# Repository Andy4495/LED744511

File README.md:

# 74'4511 BCD to 7-Segment LED Library

This library for Arduino or Energia is designed to interface with the 74'4511 BCD to Seven Segment LED driver chip. The library also supports the use of an optional 74HC164 parallel out serial shift register to reduce output pin requirements.

The library supports either one or two 7-segment displays.

A reference design which can be used with the library is available in the [extras/hardware][1] folder.

## Supported Configurations

### Parallel-only Configuration

For a single digit, a minimum of 5 output pins are required:

+ BCD bit 3 (msb)
+ BCD bit 2
+ BCD bit 1
+ BCD bit 0 (lsb)
+ /LE (Latch Enable)
+ You can also optionally define the /LT and /BL signals

For two digit setups, a minimum of 6 output pins are required:

+ BCD bit 3 (msb)
+ BCD bit 2
+ BCD bit 1
+ BCD bit 0 (lsb)
+ /LE_1 (Latch Enable for most significant digit)
+ /LE_0 (Latch Enable for least significant digit)
+ You can also optionally define the /LT and /BL signals

### Serial Configuration with 74HC164

To reduce output pin usage with the 74HC164, the library assumes that the '164 pins are connected to the '4511 pins as follows:

```text
164    4511
---    ----
 QH ->  D0
 QG ->  D1
 QF ->  D2
 QE ->  D3
```

Output pins QA - QD are not used. A and B input pins should be tied together and are controlled by the "DATA_IN" pin.

For a single digit, a minimum of 3 output pins are required:

+ CLK
+ DATA_IN
+ /LE (Latch Enable)
+ You can also optionally define the /CLR ('164), /LT ('4511) and /BL ('4511) signals

For two digit setups, a minimum of 4 output pins are required:

+ CLK
+ DATA_IN
+ /LE_1 (Latch Enable for most significant digit)
+ /LE_0 (Latch Enable for least significant digit)
+ You can also optionally define the /CLR ('164), /LT ('4511) and /BL ('4511) signals

#### Decimal Points

In the serial configuration, it is possible to control the decimal points (8th segment) of the LED displays by using the unused output pins on the 74HC164 chip. Connect QD to the most significant decimal point driver signal and QC to the least significant decimal point driver signal. Note that both decimal point driver signals need current-limiting resistors, just like all the other LED segments controlled by the '4511 BCD chip.

To control the decimal points, first store the values with the `setDP(ms, ls)` method, and then call `writeBCD()` to send the values out the shift register and change the decimal point control lines.

## Usage

_See the sketches included in the `examples` folder._

First, include the library header file:

```cpp
#include "LED744511.h"
```

Next, create an LED object. There are multiple forms for the constructor, depending on the configuration and whether you are using one or two 7-segment digits.

### Single Digit, Parallel Configuration

```cpp
LED744511 myLED(BCD3, BCD2, BCD1, BCD0, BCDLE);
```

This creates a single-digit 7-segment object which does not control the /LT or /BL pins (they are assumed to be tied high). It uses 5 output pins.

```cpp
LED744511 myLED(BCD3, BCD2, BCD1, BCD0, BCDLE, LT, BL);
```

This creates a single-digit 7-segment object which also controls the /LT and /BL pins. It uses 7 output pins.

### Double Digit, Parallel Configuration

```cpp
LED744511 myLED(BCD3, BCD2, BCD1, BCD0, BCDLE1, BCDLE0);
```

This creates a two-digit 7-segment object which does not control the /LT or /BL pins (they are assumed to be tied high). It uses 6 output pins. BCDLE1 is the most significant digit (tens) and BCDLE0 is the least significant digit (ones).

```cpp
LED744511 myLED(BCD3, BCD2, BCD1, BCD0, BCDLE1, BCDLE0, LT, BL);
```

This creates a two-digit 7-segment object which also controls the /LT and /BL pins. It uses 8 output pins.

### Single Digit, Serial Configuration

```cpp
LED744511_Serial myLED(CLK, DATA_IN, BCDLE);
```

This creates a single-digit 7-segment object which does not control the /LT or /BL pins (they are assumed to be tied high). It uses 3 output pins.

```cpp
LED744511_Serial myLED(CLK, DATA_IN, BCDLE, CLR, LT, BL);
```

This creates a single-digit 7-segment object which also controls the /CLR, /LT and /BL pins. It uses 6 output pins.

### Double Digit, Serial Configuration

```cpp
LED744511_Serial myLED(CLK, DATA_IN, BCDLE1, BCDLE0);
```

This creates a two-digit 7-segment object which does not control the /LT or /BL pins (they are assumed to be tied high). It uses 4 output pins. BCDLE1 is the most significant digit (tens) and BCDLE0 is the least significant digit (ones).

```cpp
LED744511_Serial myLED(CLK, DATA_IN, BCDLE1, BCDLE0, CLR, LT, BL);
```

This creates a two-digit 7-segment object which also controls the /CLR, /LT and /BL pins. It uses 6 output pins.

### Controlling the Displays

Once you have created an LED744511 or LED744511_Serial object, the following methods can be used to control the displays:

```cpp
void writeBCD(int value)
```

Writes `value` to the display. When used with the LED744511_Serial object, the `writeBCD()` method will also change the decimal point control signals if QD and QC are connected to the decimal point control lines. See `setDP()` below.

Negative values blank the display.

On a single-digit display, a positive value is displayed modulus 10. For example, a value of 22 will be displayed as 2.

For two-digit displays, there is a mechanism to display a leading blank or leading zero for values less than 10.

+ To display a leading blank, then use a value less than 10.
+ To display a leading zero, then use a value from 100 to 109.

For example:

+ `writeBCD(-1)` will blank both digits of the display (all segments off)
+ `writeBCD(9)` will display a leading blank and the digit 9: `9`
+ `writeBCD(109)` will display a leading 0 and the digit 9: `09`

```cpp
void lampTest(int onoff);
```

Enables or disables the /LT (Lamp Test) signal. Since it is an active-low signal, a value of 0 will turn it on, and a value of 1 will turn it off.

This function only has an effect if the LT pin was defined in the constructor.

```cpp
void blankDisplay(int onoff);
```

Enables or disables the /BL (Blank Display) signal. Since it is an active-low signal, a value of 0 will turn it on, and a value of 1 will turn it off.

This function only has an effect if the BL pin was defined in the constructor.

```cpp
void clr74HC164(int onoff);
```

Enables or disables the /CLR (register clear) signal on the '164 chip. Since it is an active-low signal, a value of 0 will turn it on, and a value of 1 will turn it off.

This method is only available in the LED744511_Serial object, and only has an effect if the CLR pin was defined in the constructor.

```cpp
void setDP(int ms, int ls);  
```

This method sets the most signifcant (ms) and least significant (ls) decimal point stored values when using the LED744511_Serial object type (the values default to zero when an instance is created). This command does not change the decimal point control signals itself. You must follow this with a `writeBCD()` to actually change the decimal point signal levels.

## References

+ 74'4511 [Datasheet](http://www.ti.com/lit/ds/symlink/cd74hc4511.pdf)
+ 74HC1164 [Datasheet](http://www.ti.com/lit/ds/symlink/sn74hc164.pdf)
+ Reference [design][1]

## License

The software and other files in this repository are released under what is commonly called the [MIT License][100]. See the file [`LICENSE`][101] in this repository.

[1]: ./extras/hardware
[100]: https://choosealicense.com/licenses/mit/
[101]: ./LICENSE
[//]: # ([200]: https://github.com/Andy4495/LED744511)

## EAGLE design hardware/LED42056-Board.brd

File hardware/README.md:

Seven Segment Interface Board Design
====================================

This is a reference design (schematic and PCB) to use with the LED744511 library.

It uses 42056-type 7-segment LED digits and 74HC4511 driver chips. It also supports an optional 74HC164 serial-to-parallel shift register for slightly reduced pin requirements.

If using the 74HC164 shift register, then connect VCC, GND, CLK, DIN, LE-MSB, and LE-LSB pins to the microcontroller.

If not using the 74HC164 shift register, then connect VCC, GND, D0, D1, D2, D3, LE-MSB, and LE-LSB pins to the microcontroller.

The /CLR, /LT, and /BT pins should have a weak pull-up (10K) resistor populated on the board. It should not normally be necessary to control those signals, but header pins are available if desired.

Note that the circuit only uses 4 bits of the shift register (QE, QF, QG, QH) - those pins are connected in parallel to the data-in bits on the 74HC4511 chips. The LE-MSB and LE-LSB pins are used to control which driver chip is being addressed. The other 4 bits (QA, QB, QC, QD) are brought out to a separate header and could potentially be used for other functions external to the board. 

References
----------
+ 74'4511 [Datasheet](http://www.ti.com/lit/ds/symlink/cd74hc4511.pdf)
+ 74HC1164 [Datasheet](http://www.ti.com/lit/ds/symlink/sn74hc164.pdf)

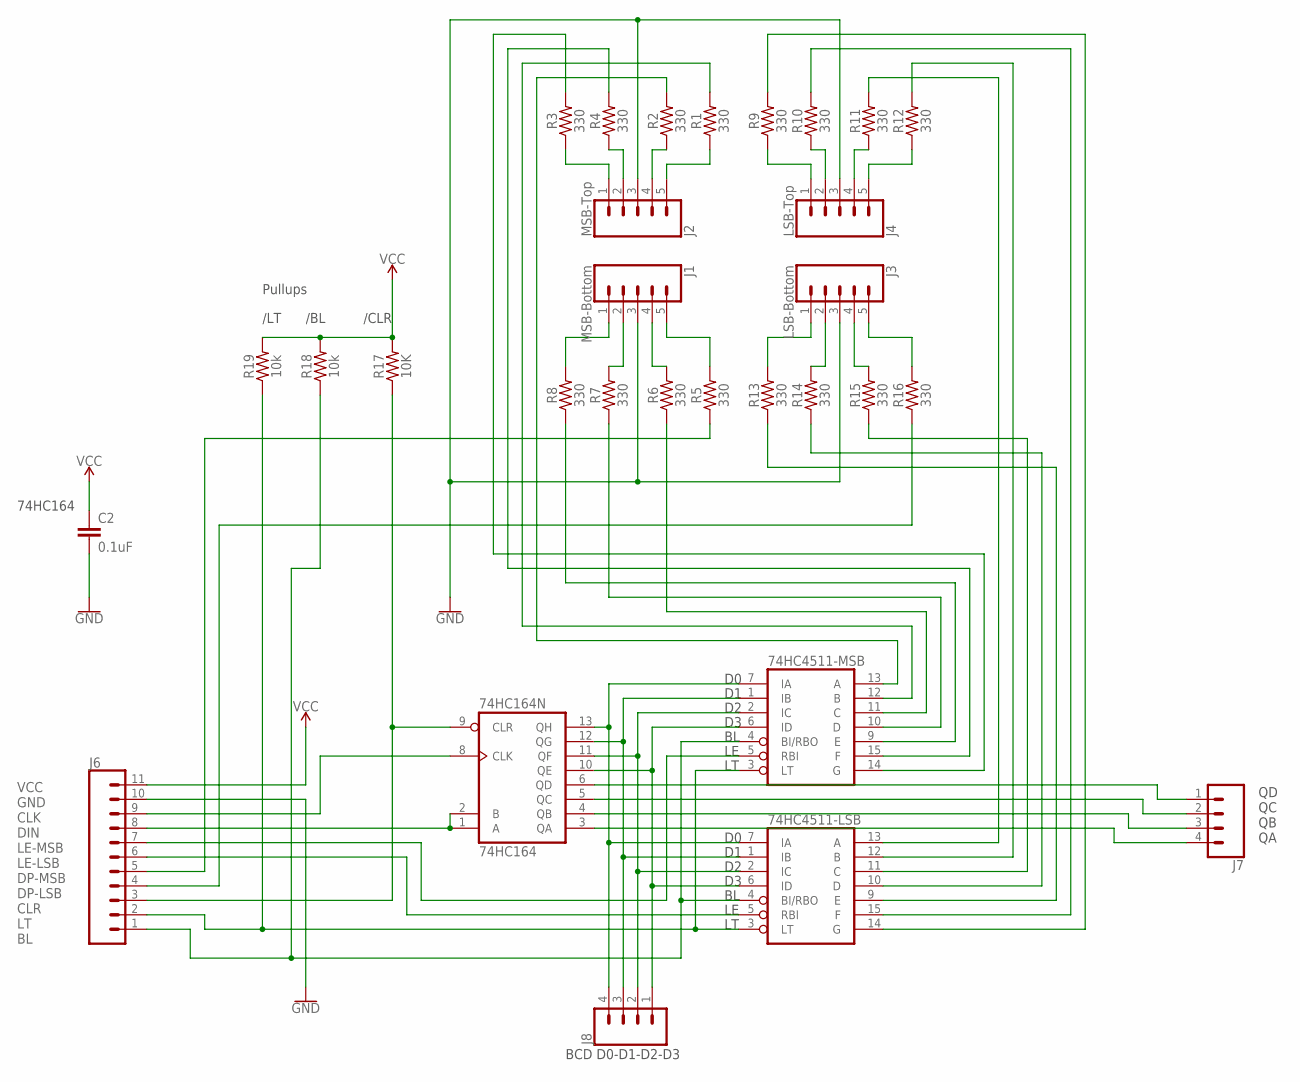
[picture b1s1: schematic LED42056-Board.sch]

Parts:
74HC164: 74HC164N; DIL14
74HC4511-LSB, 74HC4511-MSB: 74LS47N; DIL16
C2: 0.1uF; CAP-PTH-2.54
J1: MSB-Bottom; 1X05_LOCK
J2: MSB-Top; 1X05_LOCK
J3: LSB-Bottom; 1X05_LOCK
J4: LSB-Top; 1X05_LOCK
J6: CONN_11LOCK; 1X11_LOCK
J7, J8: CONN_04LOCK; 1X04_LOCK
R1, R2, R3, R4, R5, R6, R7, R8, R9, R10, R11, R12, R13, R14, R15, R16: 330; AXIAL-0.3
R17: 10K; AXIAL-0.3
R18, R19: 10k; AXIAL-0.3

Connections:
GND: 74HC164.7 (GND), 74HC4511-LSB.8 (GND), 74HC4511-MSB.8 (GND), C2.2, J1.3, J2.3, J3.3, J4.3, J6.10
unnamed: J2.1, R3.P$1 (1)
unnamed: J2.2, R4.P$1 (1)
unnamed: J2.4, R2.P$1 (1)
unnamed: J2.5, R1.P$1 (1)
unnamed: J4.1, R9.P$1 (1)
unnamed: J4.2, R10.P$1 (1)
unnamed: J4.4, R11.P$1 (1)
unnamed: J4.5, R12.P$1 (1)
unnamed: J3.5, R16.P$2 (2)
unnamed: J3.4, R15.P$2 (2)
unnamed: J3.2, R14.P$2 (2)
unnamed: J3.1, R13.P$2 (2)
unnamed: J1.5, R5.P$2 (2)
unnamed: J1.4, R6.P$2 (2)
unnamed: J1.2, R7.P$2 (2)
unnamed: J1.1, R8.P$2 (2)
unnamed: 74HC164.13 (QH), 74HC4511-LSB.7 (IA), 74HC4511-MSB.7 (IA), J8.4
unnamed: 74HC164.12 (QG), 74HC4511-LSB.1 (IB), 74HC4511-MSB.1 (IB), J8.3
unnamed: 74HC164.11 (QF), 74HC4511-LSB.2 (IC), 74HC4511-MSB.2 (IC), J8.2
unnamed: 74HC164.10 (QE), 74HC4511-LSB.6 (ID), 74HC4511-MSB.6 (ID), J8.1
unnamed: 74HC164.8 (CLK), J6.9
unnamed: 74HC164.1 (A), 74HC164.2 (B), J6.8
unnamed: 74HC164.9 (CLR), J6.3, R17.P$1 (1)
unnamed: 74HC4511-MSB.5 (RBI), J6.7
unnamed: 74HC4511-LSB.5 (RBI), J6.6
unnamed: 74HC4511-LSB.4 (BI/RBO), 74HC4511-MSB.4 (BI/RBO), J6.1, R18.P$1 (1)
unnamed: 74HC4511-LSB.3 (LT), 74HC4511-MSB.3 (LT), J6.2, R19.P$1 (1)
unnamed: 74HC4511-LSB.13 (A), R11.P$2 (2)
unnamed: 74HC4511-MSB.13 (A), R2.P$2 (2)
unnamed: 74HC4511-MSB.12 (B), R1.P$2 (2)
unnamed: 74HC4511-MSB.11 (C), R6.P$1 (1)
unnamed: 74HC4511-MSB.10 (D), R7.P$1 (1)
unnamed: 74HC4511-MSB.9 (E), R8.P$1 (1)
unnamed: 74HC4511-MSB.15 (F), R4.P$2 (2)
unnamed: 74HC4511-MSB.14 (G), R3.P$2 (2)
unnamed: 74HC4511-LSB.12 (B), R12.P$2 (2)
unnamed: 74HC4511-LSB.11 (C), R15.P$1 (1)
unnamed: 74HC4511-LSB.10 (D), R14.P$1 (1)
unnamed: 74HC4511-LSB.9 (E), R13.P$1 (1)
unnamed: 74HC4511-LSB.15 (F), R10.P$2 (2)
unnamed: 74HC4511-LSB.14 (G), R9.P$2 (2)
unnamed: J6.5, R5.P$1 (1)
unnamed: J6.4, R16.P$1 (1)
unnamed: 74HC164.6 (QD), J7.1
unnamed: 74HC164.5 (QC), J7.2
unnamed: 74HC164.4 (QB), J7.3
unnamed: 74HC164.3 (QA), J7.4
VCC: 74HC164.14 (VCC), 74HC4511-LSB.16 (VCC), 74HC4511-MSB.16 (VCC), C2.1, J6.11, R17.P$2 (2), R18.P$2 (2), R19.P$2 (2)

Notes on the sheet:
VCC GND CLK DIN LE-MSB LE-LSB DP-MSB DP-LSB CLR LT BL
QD QC QB QA
BCD D0-D1-D2-D3
Pullups
/CLR
/LT
/BL
74HC164

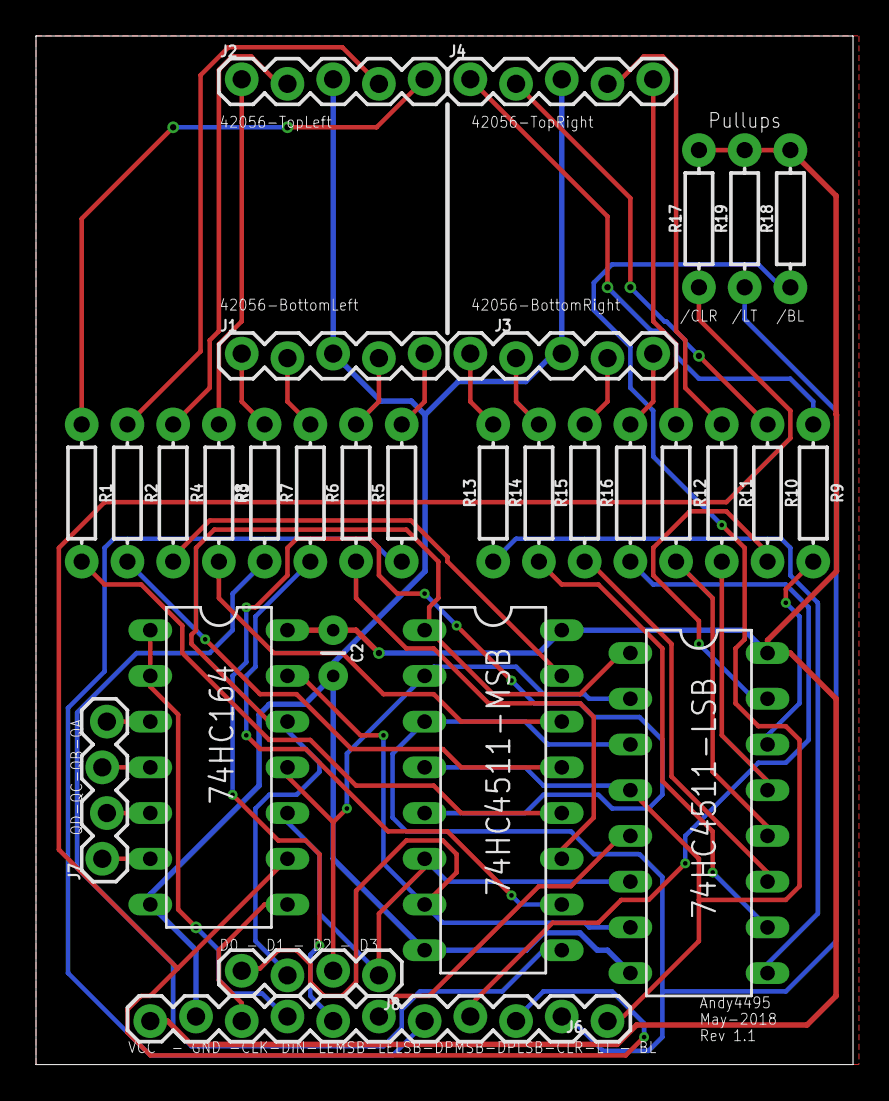
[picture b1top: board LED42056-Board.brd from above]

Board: 2 copper layers, 45.4 x 57.1 mm, 30 parts (0 on the bottom side), 49 nets.

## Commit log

2018-03-28 Initial commit.
2018-03-28 Minor README cleanup.
2018-04-08 Add LICENSE
2018-04-08 License update.
2018-04-25 Fix typos regarding /LE and /LT pins.
2018-05-18 Add support for serial mode using 74HC164 chip.
2018-05-19 Add hardware reference design.
2018-05-29 Add support to contol decimal points with serial shift register.
2019-05-08 Found and fixed typos/misspellings
2019-05-09 Fix issue with displaying leading zero, minor bit logic improvements.
2019-11-12 Update gitlab references to github.
2019-11-15 Update version since repository URL changed.
2020-01-09 Update directory structure to move hardware under extras folder.
2020-01-11 Update paragraph property.
2021-04-14 Add license info.
2021-04-30 Clean up markdownlint issues.
2022-02-25 Add .gitignore
2022-03-21 Add workflows
2022-06-18 Trigger build on dependencies
2022-06-18 Typo
2022-06-19 Split dependent repos into separate action
2022-06-27 Fix URL, update to 1.1.3
2022-07-12 Add arduino-lint action
2022-07-12 Add name to action
2022-07-29 Add build matrix avr, msp
2022-08-20 Add arduino lint badge
2022-09-08 markdownlint issues
2022-10-03 Bump actions/checkout from 2 to 3
    Bumps [actions/checkout](https://github.com/actions/checkout) from 2 to 3.
    - [Release notes](https://github.com/actions/checkout/releases)
    - [Changelog](https://github.com/actions/checkout/blob/main/CHANGELOG.md)
    - [Commits](https://github.com/actions/checkout/compare/v2...v3)
    ---
    updated-dependencies:
2023-08-24 Update for nektos/act compatibility
2023-08-30 nektos/act compatibility
2023-09-04 Bump actions/checkout from 3 to 4
    Bumps [actions/checkout](https://github.com/actions/checkout) from 3 to 4.
    - [Release notes](https://github.com/actions/checkout/releases)
    - [Changelog](https://github.com/actions/checkout/blob/main/CHANGELOG.md)
    - [Commits](https://github.com/actions/checkout/compare/v3...v4)
    ---
    updated-dependencies:
2023-09-05 Change to reusable workflows
2023-09-15 Update examples for msp432 compatibility
2023-09-15 Remove max-parallel
2023-09-17 Add create-release workflow
2024-03-08 Update cron time
2024-09-27 Use new Package Index JSON Files
2024-09-30 Switch to lychee for link checks
2024-10-01 add extra-input-files to catch all the .md files
2024-10-01 ./extras/**/*.md is now included in base action
2025-01-02 Add GCC9 to compile matrix

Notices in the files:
parts and their libraries:
SparkFun-Connectors: Licensing: Creative Commons ShareAlike 4.0 International - https://creativecommons.org/licenses/by-sa/4.0
